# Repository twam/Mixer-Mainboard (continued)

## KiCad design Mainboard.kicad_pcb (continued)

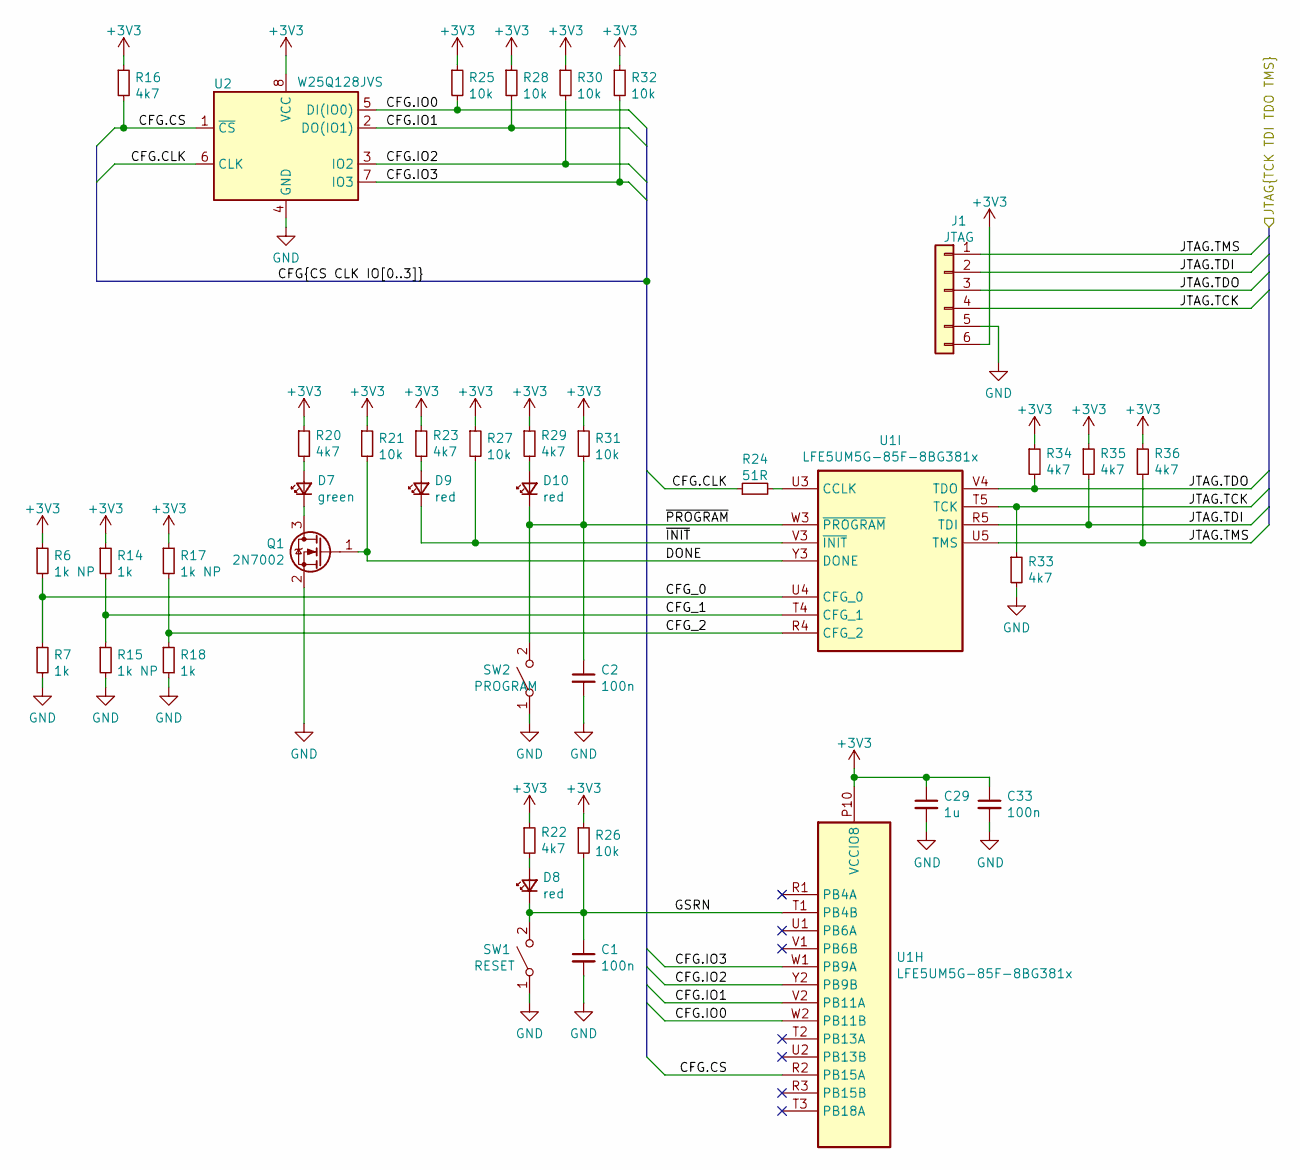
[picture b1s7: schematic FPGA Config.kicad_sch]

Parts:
C1, C2, C33: 100n; C_0402_1005Metric; LCSC C1525
C29: 1u; C_0402_1005Metric; LCSC C52923
D7: green; LED_0603_1608Metric; LCSC C72043
D8, D9, D10: red; LED_0603_1608Metric; LCSC C2286
J1: JTAG; PinHeader_1x06_P2.54mm_Vertical
Q1: 2N7002; SOT-23; LCSC C8545
R6, R15, R17: 1k NP; R_0402_1005Metric
R7, R14, R18: 1k; R_0402_1005Metric; LCSC C11702
R16, R20, R22, R23, R29, R33, R34, R35, R36: 4k7; R_0402_1005Metric; LCSC C25900
R21, R25, R26, R27, R28, R30, R31, R32: 10k; R_0402_1005Metric; LCSC C25744
R24: 51R; R_0402_1005Metric; LCSC C25125
SW1: RESET; SW_SPST_B3U-1000P; LCSC C231329
SW2: PROGRAM; SW_SPST_B3U-1000P; LCSC C231329
U1: LFE5UM5G-85F-8BG381x; Lattice_caBGA-381_17.0x17.0mm_Layout20x20_P0.8mm_Ball0.4mm_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
U2: W25Q128JVS; SOIC-8_5.23x5.23mm_P1.27mm; LCSC C97521

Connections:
+3V3: C29.1, C33.1, J1.6, R6.1, R14.1, R16.1, R17.1, R20.1, R21.1, R22.1, R23.1, R25.1, R26.1, R27.1, R28.1, R29.1, R30.1, R31.1, R32.1, R34.1, R35.1, R36.1, U1.P9 (VCCIO8), U1.P10 (VCCIO8), U2.8 (VCC); also elsewhere on the board
/Debug/JTAG.TCK: J1.4, R33.1, U1.T5 (TCK); also elsewhere on the board
/Debug/JTAG.TDI: J1.2, R35.2, U1.R5 (TDI); also elsewhere on the board
/Debug/JTAG.TDO: J1.3, R34.2, U1.V4 (TDO); also elsewhere on the board
/Debug/JTAG.TMS: J1.1, R36.2, U1.U5 (TMS); also elsewhere on the board
/FPGA Config/CFG.CLK: R24.1, U2.6 (CLK)
/FPGA Config/CFG.CS: R16.2, U1.R2 (PB15A), U2.1 (~CS)
/FPGA Config/CFG.IO0: R25.2, U1.W2 (PB11B), U2.5 (DI(IO0))
/FPGA Config/CFG.IO1: R28.2, U1.V2 (PB11A), U2.2 (DO(IO1))
/FPGA Config/CFG.IO2: R30.2, U1.Y2 (PB9B), U2.3 (IO2)
/FPGA Config/CFG.IO3: R32.2, U1.W1 (PB9A), U2.7 (IO3)
/FPGA Config/CFG_0: R6.2, R7.1, U1.U4 (CFG_0)
/FPGA Config/CFG_1: R14.2, R15.1, U1.T4 (CFG_1)
/FPGA Config/CFG_2: R17.2, R18.1, U1.R4 (CFG_2)
/FPGA Config/DONE: Q1.1 (G), R21.2, U1.Y3 (DONE)
/FPGA Config/GSRN: C1.1, D8.1 (K), R26.2, SW1.2 (B), U1.T1 (PB4B)
/FPGA Config/~INIT: D9.1 (K), R27.2, U1.V3 (~INIT)
/FPGA Config/~PROGRAM: C2.1, D10.1 (K), R31.2, SW2.2 (B), U1.W3 (~PROGRAM)
GND: C1.2, C2.2, C29.2, C33.2, J1.5, Q1.2 (S), R7.2, R15.2, R18.2, R33.2, SW1.1 (A), SW2.1 (A), U2.4 (GND); also elsewhere on the board
unnamed: D7.1 (K), Q1.3 (D)
unnamed: D7.2 (A), R20.2
unnamed: D8.2 (A), R22.2
unnamed: D9.2 (A), R23.2
unnamed: D10.2 (A), R29.2
unnamed: R24.2, U1.U3 (CCLK)

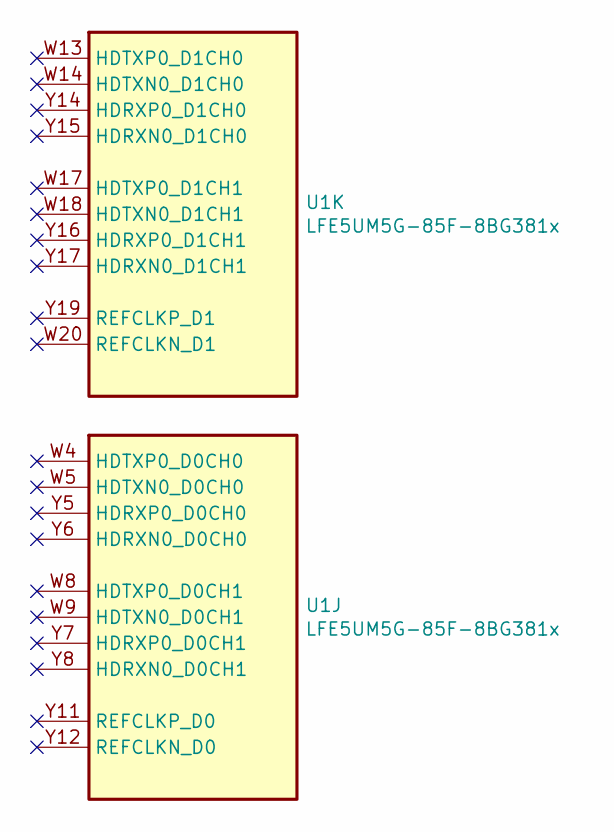
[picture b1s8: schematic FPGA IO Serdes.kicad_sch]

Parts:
U1: LFE5UM5G-85F-8BG381x; Lattice_caBGA-381_17.0x17.0mm_Layout20x20_P0.8mm_Ball0.4mm_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

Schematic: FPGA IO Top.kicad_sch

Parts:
C30, C32, C50: 100n; C_0402_1005Metric; LCSC C1525
C31: 1u; C_0402_1005Metric; LCSC C52923
R37, R38: 4k7; R_0402_1005Metric; LCSC C25900
U1: LFE5UM5G-85F-8BG381x; Lattice_caBGA-381_17.0x17.0mm_Layout20x20_P0.8mm_Ball0.4mm_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
U6: CAT24C256; SOIC-8_3.9x4.9mm_P1.27mm; LCSC C6482

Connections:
+3V3: C30.1, C31.1, C32.1, C50.1, R37.1, R38.1, U1.F9 (VCCIO0), U1.F10 (VCCIO0), U1.F11 (VCCIO1), U1.F12 (VCCIO1), U6.8 (VCC); also elsewhere on the board
/Audio IO/I2C1.SCL: U1.B8 (PT15B); also elsewhere on the board
/Audio IO/I2C1.SDA: U1.B9 (PT58A); also elsewhere on the board
/Audio IO/I2C2.SCL: U1.B12 (PT71A); also elsewhere on the board
/Audio IO/I2C2.SDA: U1.B13 (PT78A); also elsewhere on the board
/Audio IO/I2C3.SCL: U1.B16 (PT110B); also elsewhere on the board
/Audio IO/I2C3.SDA: U1.B17 (PT114A); also elsewhere on the board
/Audio IO/I2S1.BCLK: U1.B11 (PT65A); also elsewhere on the board
/Audio IO/I2S1.LRCLK: U1.A10 (PT63A); also elsewhere on the board
/Audio IO/I2S1.MCLK: U1.A11 (PT63B); also elsewhere on the board
/Audio IO/I2S1.SDIN: U1.B10 (PT60B); also elsewhere on the board
/Audio IO/I2S2.BCLK: U1.B15 (PT105A); also elsewhere on the board
/Audio IO/I2S2.LRCLK: U1.A14 (PT83A); also elsewhere on the board
/Audio IO/I2S2.MCLK: U1.A15 (PT103A); also elsewhere on the board
/Audio IO/I2S2.SDIN: U1.C14 (PT83B); also elsewhere on the board
/Audio IO/I2S3.BCLK: U1.B19 (PT119B); also elsewhere on the board
/Audio IO/I2S3.LRCLK: U1.A18 (PT119A); also elsewhere on the board
/Audio IO/I2S3.MCLK: U1.A19 (PT121A); also elsewhere on the board
/Audio IO/I2S3.SDIN: U1.B18 (PT116B); also elsewhere on the board
/Audio IO/I2S4.BCLK: U1.C6 (PT11A); also elsewhere on the board
/Audio IO/I2S4.LRCLK: U1.D7 (PT9B); also elsewhere on the board
/Audio IO/I2S4.MCLK: U1.D6 (PT6B); also elsewhere on the board
/Audio IO/I2S4.SDOUT: U1.C7 (PT11B); also elsewhere on the board
/Audio IO/I2S5.BCLK: U1.D8 (PT13B); also elsewhere on the board
/Audio IO/I2S5.LRCLK: U1.C9 (PT54A); also elsewhere on the board
/Audio IO/I2S5.MCLK: U1.C8 (PT15A); also elsewhere on the board
/Audio IO/I2S5.SDOUT: U1.C10 (PT58B); also elsewhere on the board
/Audio IO/IRQ1: U1.A8 (PT18B); also elsewhere on the board
/Audio IO/IRQ2: U1.A12 (PT76A); also elsewhere on the board
/Audio IO/IRQ3: U1.A16 (PT110A); also elsewhere on the board
/Audio IO/Mute1: U1.A9 (PT60A); also elsewhere on the board
/Audio IO/Mute2: U1.A13 (PT76B); also elsewhere on the board
/Audio IO/Mute3: U1.A17 (PT116A); also elsewhere on the board
/FPGA IO Top/SCL: R38.2, U1.A6 (PT4A), U6.6 (SCL)
/FPGA IO Top/SDA: R37.2, U1.B6 (PT4B), U6.5 (SDA)
GND: C30.2, C31.2, C32.2, C50.2, U6.1 (A0), U6.2 (A1), U6.3 (A2), U6.4 (GND), U6.7 (WP); also elsewhere on the board

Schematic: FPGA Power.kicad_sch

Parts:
C34, C36, C38, C40, C42, C44, C46, C48: 1u; C_0402_1005Metric; LCSC C52923
C35, C37, C39, C41, C43, C45, C47, C49: 100n; C_0402_1005Metric; LCSC C1525
U1: LFE5UM5G-85F-8BG381x; Lattice_caBGA-381_17.0x17.0mm_Layout20x20_P0.8mm_Ball0.4mm_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

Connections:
+1V2: C42.1, C43.1, C44.1, C45.1, C46.1, C47.1, C48.1, C49.1, U1.H8 (VCC), U1.H9 (VCC), U1.H10 (VCC), U1.H11 (VCC), U1.H12 (VCC), U1.H13 (VCC), U1.J8 (VCC), U1.J13 (VCC), U1.K8 (VCC), U1.K13 (VCC), U1.L8 (VCC), U1.L13 (VCC), U1.M8 (VCC), U1.M13 (VCC), U1.N8 (VCC), U1.N9 (VCC), U1.N10 (VCC), U1.N11 (VCC), U1.N12 (VCC), U1.N13 (VCC), U1.T6 (VCCA0), U1.T7 (VCCHTX0_D0CH0), U1.T10 (VCCHTX1_D0CH1), U1.T11 (VCCHTX0_D1CH0), U1.T14 (VCCHTX1_D1CH1), U1.T15 (VCCA1), U1.U6 (VCCA0), U1.U15 (VCCA1); also elsewhere on the board
+2V5: C34.1, C35.1, C36.1, C37.1, C38.1, C39.1, C40.1, C41.1, U1.F6 (VCCAUX), U1.F15 (VCCAUX), U1.P6 (VCCAUX), U1.P15 (VCCAUX); also elsewhere on the board
GND: C34.2, C35.2, C36.2, C37.2, C38.2, C39.2, C40.2, C41.2, C42.2, C43.2, C44.2, C45.2, C46.2, C47.2, C48.2, C49.2, U1.B7 (GND), U1.B14 (GND), U1.C19 (GND), U1.D4 (GND), U1.F7 (GND), U1.F8 (GND), U1.F13 (GND), U1.F14 (GND), U1.G4 (GND), U1.G6 (GND), U1.G7 (GND), U1.G8 (GND), U1.G9 (GND), U1.G10 (GND), U1.G11 (GND), U1.G12 (GND), U1.G13 (GND), U1.G14 (GND), U1.G15 (GND), U1.G17 (GND), U1.H19 (GND), U1.J2 (GND), U1.J7 (GND), U1.J9 (GND), U1.J10 (GND), U1.J11 (GND), U1.J12 (GND), U1.J14 (GND), U1.K6 (GND), U1.K7 (GND), U1.K9 (GND), U1.K10 (GND), U1.K11 (GND), U1.K12 (GND), U1.K14 (GND), U1.K15 (GND), U1.L9 (GND), U1.L10 (GND), U1.L11 (GND), U1.L12 (GND), U1.M2 (GND), U1.M7 (GND), U1.M9 (GND), U1.M10 (GND), U1.M11 (GND), U1.M12 (GND), U1.M14 (GND), U1.M16 (GND), U1.N6 (GND), U1.N7 (GND), U1.N14 (GND), U1.N15 (GND), U1.P7 (GND), U1.P8 (GND), U1.P11 (GND), U1.P12 (GND), U1.P13 (GND), U1.P14 (GND), U1.R19 (GND), U1.U7 (GND), U1.U8 (GND), U1.U9 (GND), U1.U10 (GND), U1.U11 (GND), U1.U12 (GND), U1.U13 (GND), U1.U14 (GND), U1.V5 (GND), U1.V6 (GND), U1.V7 (GND), U1.V8 (GND), U1.V9 (GND), U1.V12 (GND), U1.V13 (GND), U1.V14 (GND), U1.V15 (GND), U1.V16 (GND), U1.V19 (GND), U1.V20 (GND), U1.W6 (GND), U1.W7 (GND), U1.W12 (GND), U1.W15 (GND), U1.W16 (GND), U1.W19 (GND); also elsewhere on the board

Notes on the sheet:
V_CC (Core): 1.2 V V_CCAUX (Aux): 2.5 V V_CCA (SERDES Analog): 1.2 V (connected to V_CC if unused) V_CCAUXA (SERDES Aux): 2.5 V (open if unused) V_CCHRX (SERDES Input Buffer): 1.2 V (open if unused) V_CCHTX (SERDES Output Buffer): 1.2 V (open/V_CCA if unused)

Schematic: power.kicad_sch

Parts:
C4, C5, C6: 4u7; C_0603_1608Metric; LCSC C19666
C7, C8, C9: 6p8; C_0402_1005Metric; LCSC C1576
C10, C11, C16, C17: 10u; C_0603_1608Metric; LCSC C19702
C12, C18: 22u; C_0603_1608Metric; LCSC C59461
C13, C14, C15: 1u; C_0603_1608Metric; LCSC C15849
D1, D2: green; LED_0603_1608Metric; LCSC C72043
D12: red; LED_0603_1608Metric; LCSC C2286
F1: 2A; Fuse_0603_1608Metric_Pad1.05x0.95mm_HandSolder; LCSC C187605
J2: Power; JST_VH_B4P-VH_1x04_P3.96mm_Vertical
L3, L4, L5: 2u2; L_0805_2012Metric; LCSC C216156
R1, R9: 15k; R_0402_1005Metric; LCSC C25756
R2, R43: 4k7; R_0402_1005Metric; LCSC C25900
R8: 68k; R_0402_1005Metric; LCSC C36871
R10: 150k; R_0402_1005Metric; LCSC C25755
R11: 47k; R_0402_1005Metric; LCSC C25792
R12, R13: 100k; R_0402_1005Metric; LCSC C25741
TP4: 3V3; TestPoint_Pad_D1.5mm
TP5: 2V5; TestPoint_Pad_D1.5mm
TP6: 1V2; TestPoint_Pad_D1.5mm
U3, U4, U5: TLV62569DBV; SOT-23-5; LCSC C141836

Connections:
+1V2: C9.1, C12.1, C15.1, C18.1, L5.2, R12.1, TP6.1; also elsewhere on the board
+2V5: C8.1, C11.1, C14.1, C17.1, L4.2, R10.1, TP5.1; also elsewhere on the board
+3V3: C7.1, C10.1, C13.1, C16.1, L3.2, R2.1, R8.1, TP4.1; also elsewhere on the board
+5V: C4.2, C5.2, C6.2, F1.2, R1.1, R43.1, U3.1 (EN), U3.4 (VIN), U4.1 (EN), U4.4 (VIN), U5.1 (EN), U5.4 (VIN)
/Power/PWR_IN: D12.2 (A), F1.1, J2.1, J2.2
GND: C4.1, C5.1, C6.1, C10.2, C11.2, C12.2, C13.2, C14.2, C15.2, C16.2, C17.2, C18.2, D1.1 (K), D2.1 (K), J2.3, J2.4, R9.2, R11.2, R13.2, U3.2 (GND), U4.2 (GND), U5.2 (GND); also elsewhere on the board
unnamed: C7.2, R8.2, R9.1, U3.5 (FB)
unnamed: C8.2, R10.2, R11.1, U4.5 (FB)
unnamed: C9.2, R12.2, R13.1, U5.5 (FB)
unnamed: D1.2 (A), R1.2
unnamed: D2.2 (A), R2.2
unnamed: D12.1 (K), R43.2
unnamed: L3.1, U3.3 (SW)
unnamed: L4.1, U4.3 (SW)
unnamed: L5.1, U5.3 (SW)

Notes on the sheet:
3.3V
2.5V
1.2V

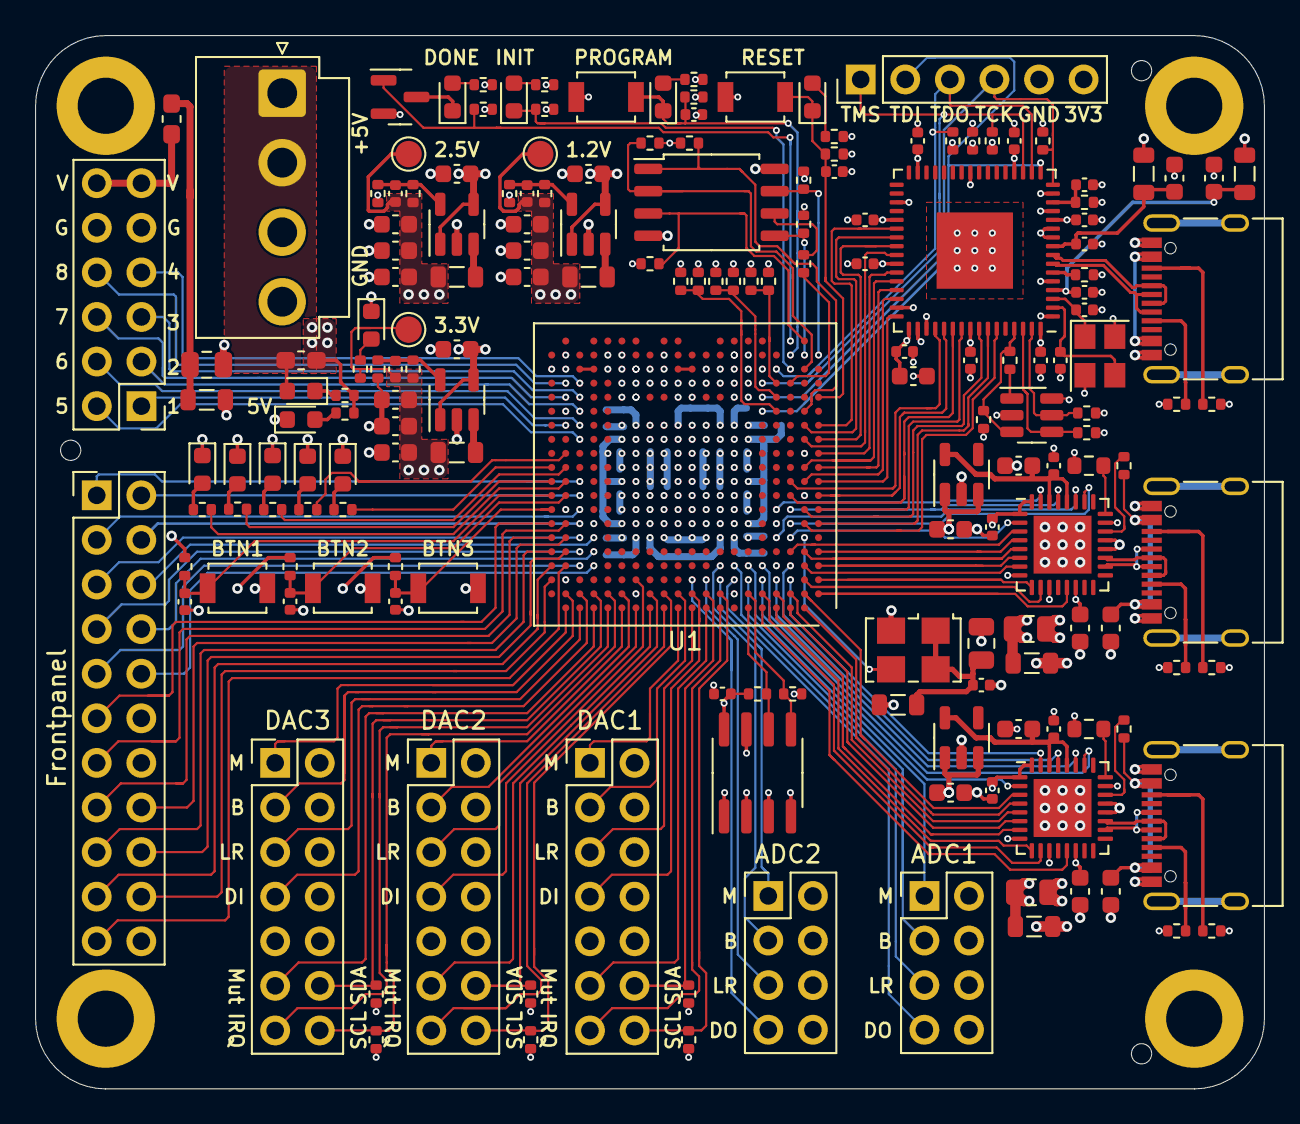
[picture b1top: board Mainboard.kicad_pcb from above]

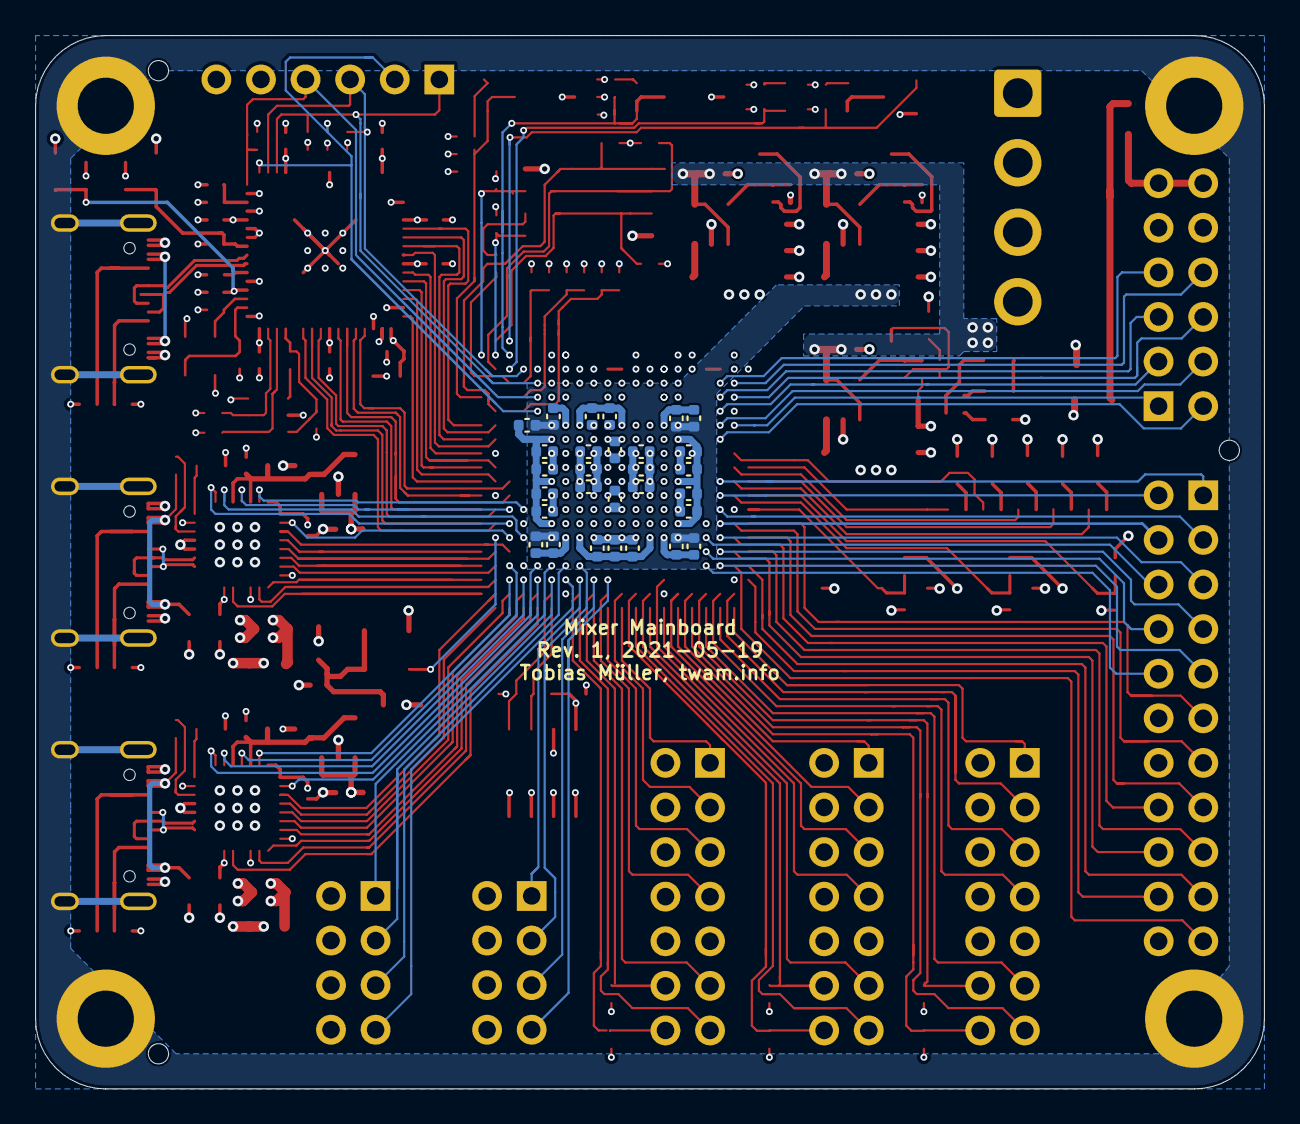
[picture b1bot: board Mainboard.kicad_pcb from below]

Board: 4 copper layers, 70.0 x 60.0 mm, 213 parts (29 on the bottom side), 193 nets.

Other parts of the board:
C101: 10u; C_0805_2012Metric
C102: 1u; C_0603_1608Metric
C103: 10u; C_0603_1608Metric
C104, C106: 2u2; C_0603_1608Metric
C105, C107: 100n; C_0402_1005Metric
J101: USB1; USB_C_Receptacle_XKB_TYPE-C-31-M-12
L101: 600R/100M; L_0805_2012Metric
R101, R102: 5k1; R_0402_1005Metric
R104: 10k; R_0402_1005Metric
R105: 8k06 1%; R_0603_1608Metric
U101: USB3320; QFN-32-1EP_5x5mm_P0.5mm_EP3.3x3.3mm
U102: TPS76318; SOT-23-5

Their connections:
+3V3: L101.1; also elsewhere on the board
/FPGA IO Left/ULPI1.CLK: U101.26 (REFCLK); also elsewhere on the board
/FPGA IO Left/ULPI1.DIR: U101.31 (DIR); also elsewhere on the board
/FPGA IO Left/ULPI1.D_{0}: U101.3 (DATA0); also elsewhere on the board
/FPGA IO Left/ULPI1.D_{1}: U101.4 (DATA1); also elsewhere on the board
/FPGA IO Left/ULPI1.D_{2}: U101.5 (DATA2); also elsewhere on the board
/FPGA IO Left/ULPI1.D_{3}: U101.6 (DATA3); also elsewhere on the board
/FPGA IO Left/ULPI1.D_{4}: U101.7 (DATA4); also elsewhere on the board
/FPGA IO Left/ULPI1.D_{5}: U101.9 (DATA5); also elsewhere on the board
/FPGA IO Left/ULPI1.D_{6}: U101.10 (DATA6); also elsewhere on the board
/FPGA IO Left/ULPI1.D_{7}: U101.13 (DATA7); also elsewhere on the board
/FPGA IO Left/ULPI1.NXT: U101.2 (NXT); also elsewhere on the board
/FPGA IO Left/ULPI1.RST: U101.27 (RESETB); also elsewhere on the board
/FPGA IO Left/ULPI1.STP: U101.29 (STP); also elsewhere on the board
/USB1/1V8_USB: C103.1, C107.1, U101.28 (VDD18), U101.30 (VDD18), U102.5 (VOUT)
/USB1/3V3_USB: C101.1, C102.1, C105.1, C106.1, L101.2, U101.1 (CLKOUT), U101.8 (REFSEL0), U101.11 (REFSEL1), U101.14 (REFSEL2), U101.20 (VDD33), U101.21 (VBAT), U101.23 (ID), U101.32 (VDDIO), U102.1 (VIN), U102.3 (EN)
/USB1/CC1: J101.A5 (CC1), R101.2
/USB1/CC2: J101.B5 (CC2), R102.2
/USB1/D+: J101.A6 (D+), J101.B6 (D+), U101.18 (DP)
/USB1/D-: J101.A7 (D-), J101.B7 (D-), U101.19 (DM)
/USB1/VBUS: C104.1, J101.A4 (VBUS), J101.A9 (VBUS), J101.B4 (VBUS), J101.B9 (VBUS), R104.1
Earth: J101.S1 (SHIELD); also elsewhere on the board
GND: C101.2, C102.2, C103.2, C104.2, C105.2, C106.2, C107.2, J101.A1 (GND), J101.A12 (GND), J101.B1 (GND), J101.B12 (GND), R101.1, R102.1, R105.2, U101.33 (GND), U102.2 (GND); also elsewhere on the board
unnamed: R104.2, U101.22 (VBUS)
unnamed: R105.1, U101.24 (RBIAS)

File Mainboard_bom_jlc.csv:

"Comment","Designator","Footprint","LCSC Part #"
"6p8","C7,C8,C9","C_0402_1005Metric","C1576"
"22u","C12,C18","C_0603_1608Metric","C59461"
"1u","C29,C34,C36,C38,C40,C42,C44,C46,C48,C21,C23,C31,C25,C27","C_0402_1005Metric","C52923"
"10u","C101,C201,C19,C3","C_0805_2012Metric","C15850"
"1u","C102,C202,C13,C14,C15","C_0603_1608Metric","C15849"
"10u","C103,C203,C10,C11,C16,C17","C_0603_1608Metric","C19702"
"2u2","C104,C106,C204,C206","C_0603_1608Metric","C23630"
"20pF","C501,C502","C_0402_1005Metric","C1554"
"4u7","C503,C505,C515,C4,C5,C6","C_0603_1608Metric","C19666"
"100n","C504,C506,C507,C508,C509,C510,C511,C512,C513,C514,C516,C105,C107,C205,C207,C1,C2,C33,C35,C37,C39,C41,C43,C45,C47,C49,C20,C22,C24,C30,C32,C50,C26,C28,C51,C52,C53","C_0402_1005Metric","C1525"
"yellow","D4","LED_0603_1608Metric","C72038"
"white","D5","LED_0603_1608Metric","C2290"
"blue","D6","LED_0603_1608Metric","C72041"
"green","D7,D1,D2,D3","LED_0603_1608Metric","C72043"
"red","D8,D9,D10,D12,D11","LED_0603_1608Metric","C2286"
"2A","F1,F2","Fuse_0603_1608Metric_Pad1.05x0.95mm_HandSolder","C187605"
"USB1","J501,J101,J201","USB_C_Receptacle_XKB_TYPE-C-31-M-12","C165948"
"600R/100M","L1,L501,L101,L201,L6,L2","L_0805_2012Metric","C1017"
"2u2","L3,L4,L5","L_0805_2012Metric","C216156"
"2N7002","Q1","SOT-23","C8545"
"15k","R1,R9","R_0402_1005Metric","C25756"
"1k","R7,R14,R18","R_0402_1005Metric","C11702"
"68k","R8","R_0402_1005Metric","C36871"
"150k","R10","R_0402_1005Metric","C25755"
"47k","R11","R_0402_1005Metric","C25792"
"100k","R12,R13","R_0402_1005Metric","C25741"
"51R","R24","R_0402_1005Metric","C25125"
"1k5","R39","R_0402_1005Metric","C25867"
"8k06 1%","R105,R205","R_0603_1608Metric","C23112"
"5k1","R501,R502,R101,R102,R201,R202","R_0402_1005Metric","C25905"
"12k","R503","R_0402_1005Metric","C25752"
"10k","R504,R505,R506,R507,R104,R204,R21,R25,R26,R27,R28,R30,R31,R32,R3,R4,R5","R_0402_1005Metric","C25744"
"2k2","R508","R_0402_1005Metric","C25879"
"4k7","R601,R602,R611,R612,R621,R622,R16,R20,R22,R23,R29,R33,R34,R35,R36,R37,R38,R2,R43,R19,R40,R41,R42","R_0402_1005Metric","C25900"
"RESET","SW1","SW_SPST_B3U-1000P","C231329"
"PROGRAM","SW2","SW_SPST_B3U-1000P","C231329"
"BTN1","SW3","SW_SPST_B3U-1000P","C231329"
"BTN2","SW4","SW_SPST_B3U-1000P","C231329"
"BTN3","SW5","SW_SPST_B3U-1000P","C231329"
"W25Q128JVS","U2","SOIC-8_5.23x5.23mm_P1.27mm","C97521"
"TLV62569DBV","U3,U4,U5","SOT-23-5","C141836"
"CAT24C256","U6","SOIC-8_3.9x4.9mm_P1.27mm","C6482"
"USB3320","U101,U201","QFN-32-1EP_5x5mm_P0.5mm_EP3.3x3.3mm","C132156"
"TPS76318","U102,U202","SOT-23-5","C7099"
"FT2232HQ","U501","QFN-64-1EP_9x9mm_P0.5mm_EP4.35x4.35mm","C193662"
"93LCxxBxxOT","U502","SOT-23-6","C190271"
"SG-5032CAN","X1","Oscillator_SMD_SeikoEpson_SG8002LB-4Pin_5.0x3.2mm","C37076"
"12M","Y501","Crystal_SMD_3225-4Pin_3.2x2.5mm","C9002"

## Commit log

2021-06-05 Initial commit. Rev 1
2022-01-07 Update to KiCad 6
2022-01-15 Add README
